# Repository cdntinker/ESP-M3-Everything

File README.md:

# ESP-M3-Everything
I little universal ESP-M3 carrier board

At some point...  I should figure out this github stuff & clean this up.

But for now, esp-m3.lib, esp-m3.dcm & foo.kicad_mod are the symbol & footprint for the ESP-M3 module.  Symbol provided by Geekboy1011 on the AddOhms discord.  The footprint is roughly based on his design too...  (But I used his footprint to figure out how to build a new one that actually worked a bit better.)

J1 & J2 are just for power.  & laid out for any of 3 options.  USB micro jack, direct connection or my favourite Chinese breakout board.

J3 is actually compatible with the pin header on most Sonoff devices (if you ignore pins 5 & 6.

If you use pins 5 & 6, you can make it act like a D1-mini when flashing firmware.

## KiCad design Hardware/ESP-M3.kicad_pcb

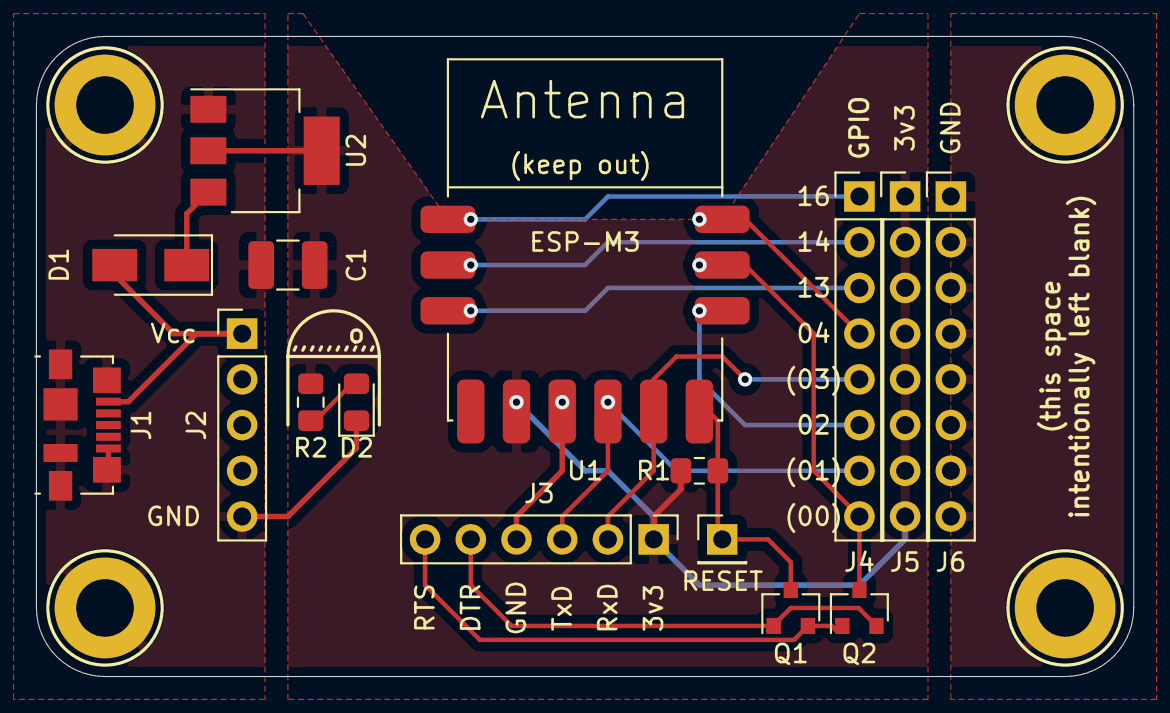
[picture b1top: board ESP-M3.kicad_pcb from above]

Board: 2 copper layers, 61.0 x 35.6 mm, 16 parts (0 on the bottom side), 16 nets.

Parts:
C1: 22uf; C_1210_3225Metric_Pad1.42x2.65mm_HandSolder
D1: MRA4003T3G; D_SMA
D2: LED; LED_0805_2012Metric_Pad1.15x1.40mm_HandSolder
J1: USB_B_Micro; USB_Micro-B_Molex_47346-0001
J2: Conn_01x05_Male; PinHeader_1x05_P2.54mm_Vertical
J3: Conn_01x06_Male; PinHeader_1x06_P2.54mm_Vertical
J4, J5, J6: Conn_01x08_Male; PinHeader_1x08_P2.54mm_Vertical
Q1, Q2: MMBT3904; SOT-23
R1, R2: 10K; R_0805_2012Metric_Pad1.15x1.40mm_HandSolder
TP1: RESET; PinHeader_1x01_P2.54mm_Vertical
U1: ESP-M3; foo
U2: AMS1117-3.3; SOT-223-3_TabPin2

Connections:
+3V3: C1.1, J3.1, J5.1, J5.2, J5.3, J5.4, J5.5, J5.6, J5.7, J5.8, R1.1, R2.2, U1.5, U2.2
+5V: D1.2, J1.1, J2.1
/DTR: J3.5, Q1.1, Q2.2
/IO0: J4.8, Q2.3, U1.11
/IO1: J3.3, J4.7, U1.7
/IO2: J4.6, U1.10
/IO3: J3.2, J4.5, U1.8
/IO4: J4.4, U1.12
/IO13: J4.3, U1.3
/IO14: J4.2, U1.2
/IO16: J4.1, U1.1
/RTS: J3.6, Q1.2, Q2.1
/Reset: Q1.3, R1.2, TP1.1, U1.9
GND: C1.2, D2.1, J1.5, J1.6, J2.5, J3.4, J6.1, J6.2, J6.3, J6.4, J6.5, J6.6, J6.7, J6.8, U1.6, U2.1
unnamed: D1.1, U2.3
unnamed: D2.2, R2.1

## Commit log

2020-09-08 Create LICENSE
    Blame the choice of licence on the Bald Engineer...
2020-09-08 Create Images
2020-09-08 Create foobar
2020-09-08 Update LICENSE
2022-03-02 Converting to new format of repo
2022-03-03 Finally... A seemingly good .gitignore.
